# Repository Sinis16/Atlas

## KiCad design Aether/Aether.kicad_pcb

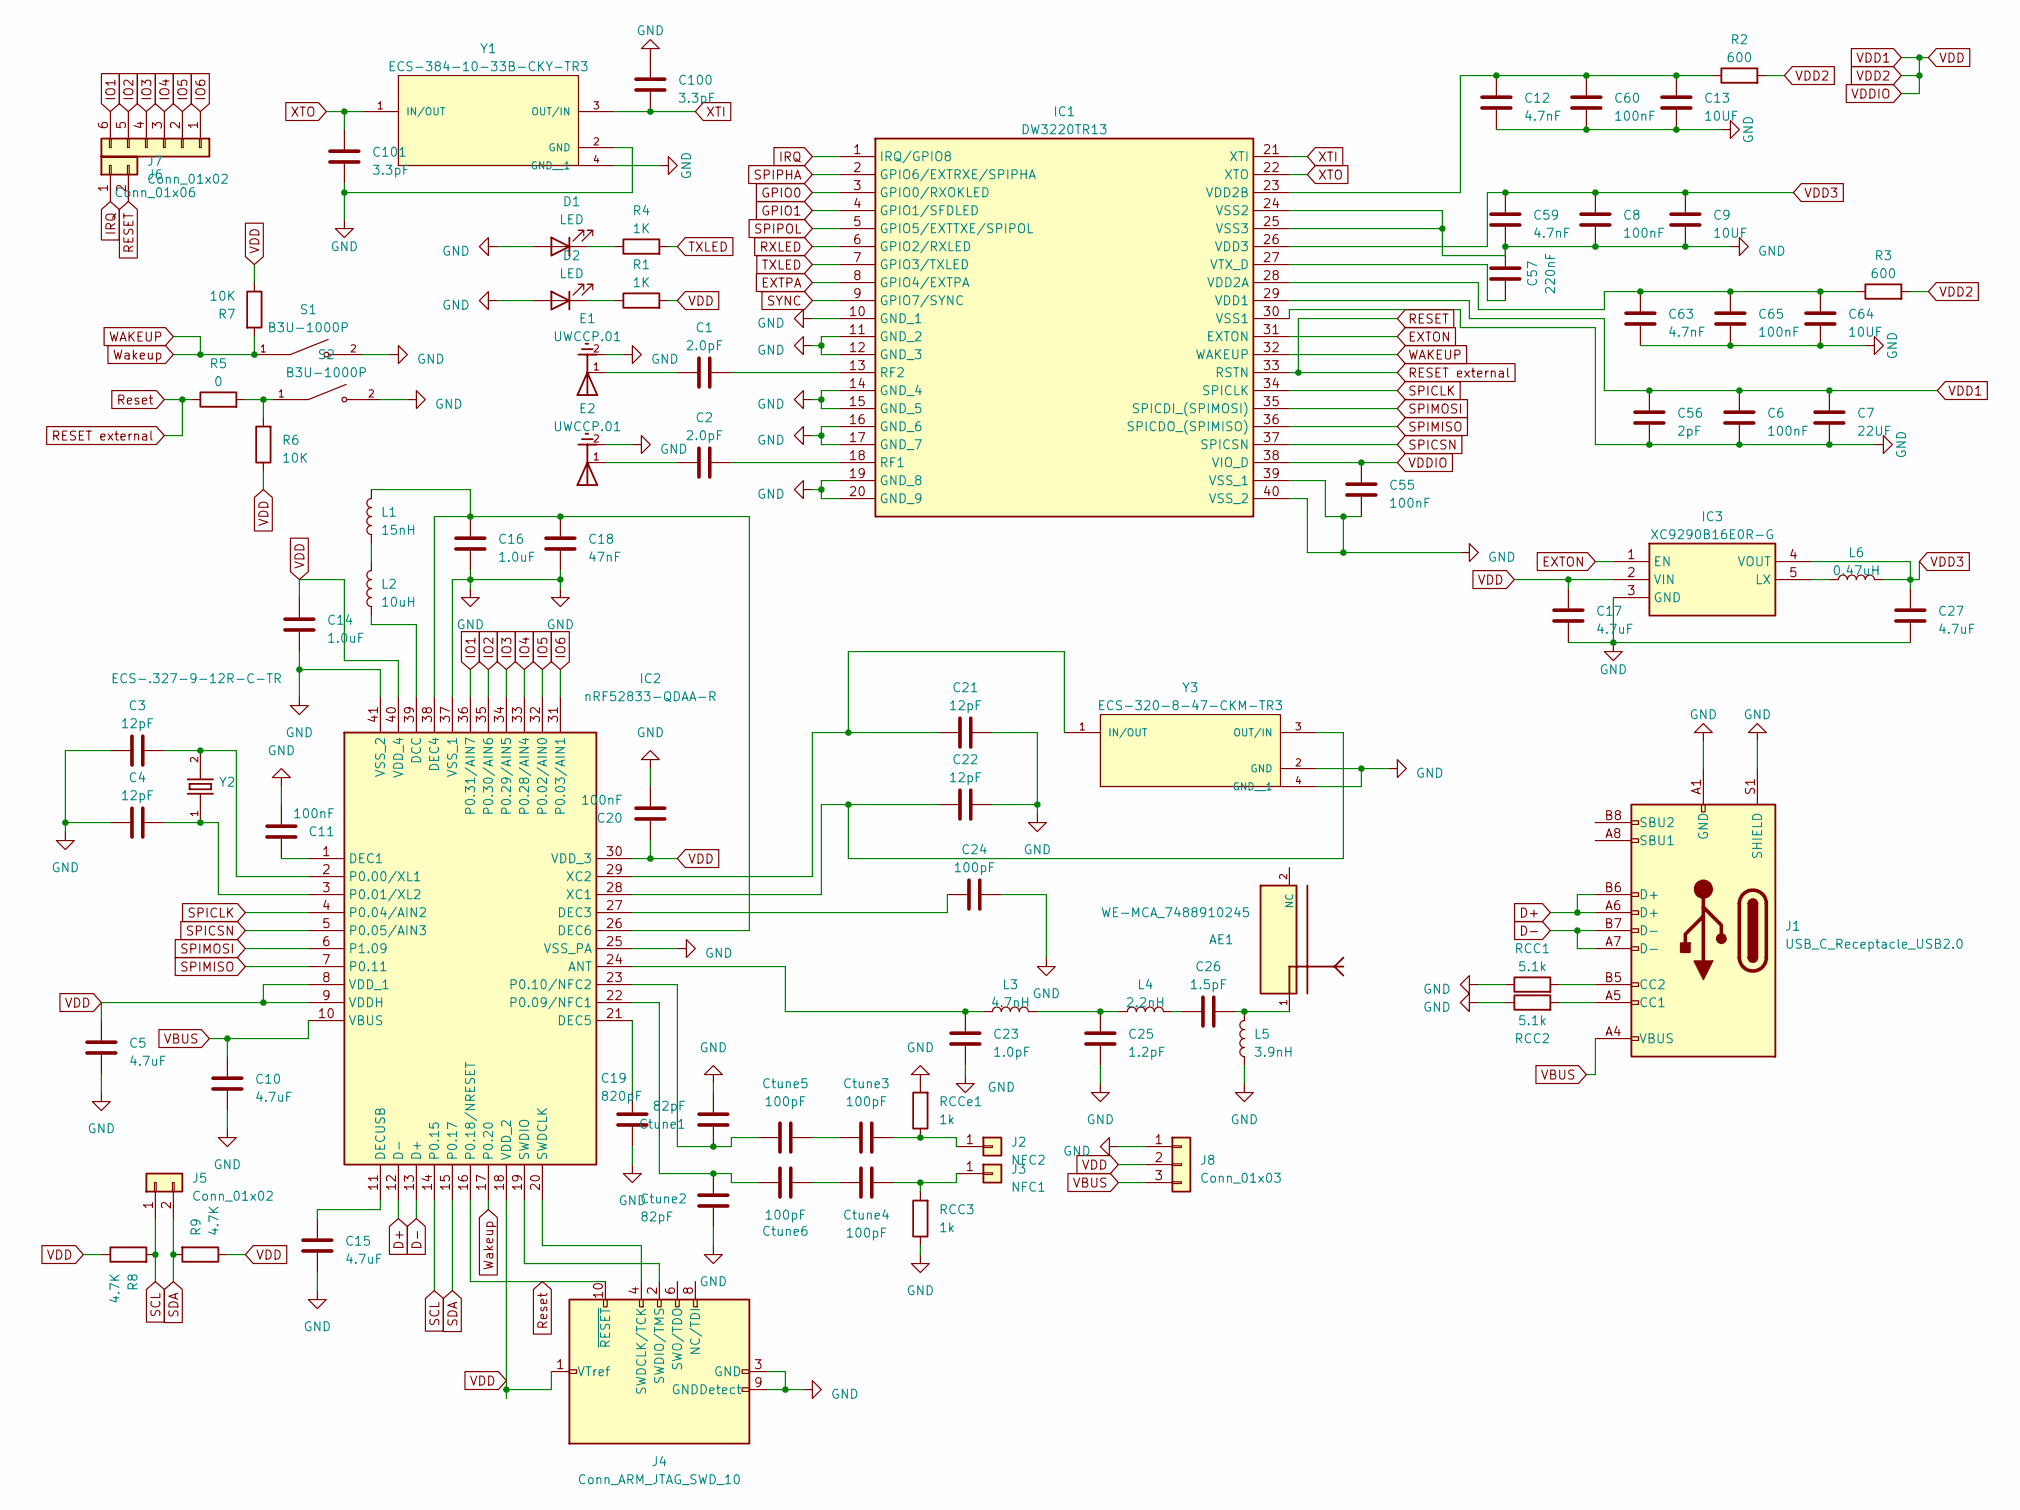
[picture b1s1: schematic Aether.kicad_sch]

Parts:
AE1: WE-MCA_7488910245; PART-NUMBER 7488910245
C1, C2: 2.0pF; C_0201_0603Metric
C3, C4, C21, C22: 12pF; C_0603_1608Metric
C5, C10, C15: 4.7uF; C_0603_1608Metric
C6, C8, C11, C20, C60, C65: 100nF; C_0603_1608Metric
C7: 22UF; C_0603_1608Metric
C9, C13, C64: 10UF; C_0603_1608Metric
C12, C59, C63: 4.7nF; C_0603_1608Metric
C14, C16: 1.0uF; C_0603_1608Metric
C17, C27: 4.7uF; C_0201_0603Metric_Pad0.64x0.40mm_HandSolder
C18: 47nF; C_0603_1608Metric
C19: 820pF; C_0603_1608Metric
C23: 1.0pF; C_0201_0603Metric_Pad0.64x0.40mm_HandSolder
C24: 100pF; C_0603_1608Metric
C25: 1.2pF; C_0201_0603Metric_Pad0.64x0.40mm_HandSolder
C26: 1.5pF; C_0201_0603Metric_Pad0.64x0.40mm_HandSolder
C55: 100nF; C_0402_1005Metric
C56: 2pF; C_0603_1608Metric
C57: 220nF; C_0603_1608Metric
C100, C101: 3.3pF; C_0603_1608Metric
Ctune1, Ctune2: 82pF; C_0603_1608Metric
Ctune3, Ctune4, Ctune5, Ctune6: 100pF; C_0805_2012Metric
D1, D2: LED; LED_0603_1608Metric
E1, E2: UWCCP.01; ANTENNA_UWCCP.01; PARTREV SPE-17-8-057/AZ
IC1: DW3220TR13; DW3220TR13-1; Manufacturer_Part_Number DW3220TR13; Mouser Part Number 772-DW3220TR13
IC2: nRF52833-QDAA-R; QFN40P500X500X90-41N; Manufacturer_Part_Number nRF52833-QDAA-R; Mouser Part Number 949-NRF52833-QDAA-R
IC3: XC9290B16E0R-G; XC9290A07E0RG; Manufacturer_Part_Number XC9290B16E0R-G; Mouser Part Number 865-XC9290B16E0R-G
J1: USB_C_Receptacle_USB2.0; USB_C_Receptacle_Palconn_UTC16-G
J2: NFC2; TestPoint_Pad_3.0x3.0mm
J3: NFC1; TestPoint_Pad_3.0x3.0mm
J4: Conn_ARM_JTAG_SWD_10; PinHeader_2x05_P1.27mm_Vertical
J5, J7: Conn_01x02; PinHeader_1x02_P2.54mm_Vertical
J6: Conn_01x06; PinHeader_1x06_P2.54mm_Vertical
J8: Conn_01x03; PinHeader_1x03_P2.54mm_Vertical
L1: 15nH; L_0603_1608Metric
L2: 10uH; L_0603_1608Metric
L3: 4.7nH; L_0201_0603Metric
L4: 2.2nH; L_0201_0603Metric
L5: 3.9nH; L_0201_0603Metric
L6: 0.47uH; L_01005_0402Metric
R1, R4: 1K; R_0603_1608Metric_Pad0.98x0.95mm_HandSolder
R2, R3: 600; R_0603_1608Metric_Pad0.98x0.95mm_HandSolder
R5: 0; R_0603_1608Metric_Pad0.98x0.95mm_HandSolder
R6, R7: 10K; R_0603_1608Metric_Pad0.98x0.95mm_HandSolder
R8, R9: 4.7K; R_0603_1608Metric_Pad0.98x0.95mm_HandSolder
RCC1, RCC2: 5.1k; R_0603_1608Metric
RCC3: 1k; R_0603_1608Metric
RCCe1: 1k; R_0603_1608Metric
S1, S2: B3U-1000P; SW_B3U-1000P
Y1: ECS-384-10-33B-CKY-TR3; XTAL_ECS-384-10-33B-CKY-TR3; PARTREV 2017
Y2: ECS-.327-9-12R-C-TR; XTAL_ECS-.327-9-12R-C-TR; PARTREV 2017
Y3: ECS-320-8-47-CKM-TR3; XTAL_ECS-320-8-47-CKM-TR3; PARTREV 2017

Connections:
D+: IC2.12 (D-), J1.A6 (D+), J1.B6 (D+)
D-: IC2.13 (D+), J1.A7 (D-), J1.B7 (D-)
EXTON: IC1.31 (EXTON), IC3.1 (EN)
EXTPA: IC1.8 (GPIO4/EXTPA)
GND: C3.2, C4.2, C5.2, C6.1, C7.1, C8.1, C9.1, C10.2, C11.2, C12.1, C13.1, C14.2, C15.2, C16.2, C17.1, C18.2, C19.2, C20.2, C21.2, C22.2, C23.2, C24.2, C25.2, C27.1, C55.1, C56.1, C57.2, C59.1, C60.2, C63.1, C64.1, C65.1, C100.2, C101.1, Ctune1.2, Ctune2.2, D1.2 (A), D2.2 (A), E1.2, E2.2, IC1.10 (GND_1), IC1.11 (GND_2), IC1.12 (GND_3), IC1.14 (GND_4), IC1.15 (GND_5), IC1.16 (GND_6), IC1.17 (GND_7), IC1.19 (GND_8), IC1.20 (GND_9), IC1.24 (VSS2), IC1.25 (VSS3), IC1.30 (VSS1), IC1.39 (VSS_1), IC1.40 (VSS_2), IC2.25 (VSS_PA), IC2.37 (VSS_1), IC2.41 (VSS_2), IC3.3 (GND), J1.A1 (GND), J1.A12 (GND), J1.B1 (GND), J1.B12 (GND), J1.S1 (SHIELD), J4.3 (GND), J4.5 (GND), J4.9 (GNDDetect), J8.1, L5.1, RCC1.1, RCC2.1, RCC3.1, RCCe1.2, S1.2, S2.2, Y1.2 (GND), Y1.4 (GND__1), Y3.2 (GND), Y3.4 (GND__1)
GPIO0: IC1.3 (GPIO0/RXOKLED)
GPIO1: IC1.4 (GPIO1/SFDLED)
IO1: IC2.36 (P0.31/AIN7), J6.6
IO2: IC2.35 (P0.30/AIN6), J6.5
IO3: IC2.34 (P0.29/AIN5), J6.4
IO4: IC2.33 (P0.28/AIN4), J6.3
IO5: IC2.32 (P0.02/AIN0), J6.2
IO6: IC2.31 (P0.03/AIN1), J6.1
IRQ: IC1.1 (IRQ/GPIO8), J7.1
unnamed: AE1.1, C26.1, L5.2
unnamed: C1.2, E1.1
unnamed: C2.2, E2.1
unnamed: C25.1, L3.2, L4.1
unnamed: C26.2, L4.2
unnamed: Ctune3.2, Ctune5.1
unnamed: Ctune4.2, Ctune6.1
unnamed: D1.1 (K), R4.1
unnamed: D2.1 (K), R1.1
unnamed: C2.1, IC1.18 (RF1)
unnamed: C1.1, IC1.13 (RF2)
unnamed: C63.2, C64.2, C65.2, IC1.28 (VDD2A), R3.1
unnamed: C12.2, C13.2, C60.1, IC1.23 (VDD2B), R2.1
unnamed: C57.1, IC1.27 (VTX_D)
unnamed: C23.1, IC2.24 (ANT), L3.1
unnamed: IC2.39 (DCC), L2.1
unnamed: C11.1, IC2.1 (DEC1)
unnamed: C24.1, IC2.27 (DEC3)
unnamed: C16.1, C18.1, IC2.26 (DEC6), IC2.38 (DEC4), L1.2
unnamed: C19.1, IC2.21 (DEC5)
unnamed: C15.1, IC2.11 (DECUSB)
unnamed: C3.1, IC2.2 (P0.00/XL1), Y2.2
unnamed: C4.1, IC2.3 (P0.01/XL2), Y2.1
unnamed: Ctune2.1, Ctune6.2, IC2.22 (P0.09/NFC1)
unnamed: Ctune1.1, Ctune5.2, IC2.23 (P0.10/NFC2)
unnamed: IC2.20 (SWDCLK), J4.4 (SWDCLK/TCK)
unnamed: IC2.19 (SWDIO), J4.2 (SWDIO/TMS)
unnamed: C22.1, IC2.28 (XC1), Y3.3 (OUT/IN)
unnamed: C21.1, IC2.29 (XC2), Y3.1 (IN/OUT)
unnamed: IC3.5 (LX), L6.1
unnamed: J1.A5 (CC1), RCC2.2
unnamed: J1.B5 (CC2), RCC1.2
unnamed: Ctune3.1, J2.1, RCCe1.1
unnamed: Ctune4.1, J3.1, RCC3.2
unnamed: L1.1, L2.2
unnamed: R5.2, R6.2, S2.1
RESET: IC1.33 (RSTN), IC2.16 (P0.18/NRESET), J4.10 (~RESET), J7.2, R5.1
RXLED: IC1.6 (GPIO2/RXLED)
SCL: IC2.14 (P0.15), J5.1, R8.2
SDA: IC2.15 (P0.17), J5.2, R9.2
SPICLK: IC1.34 (SPICLK), IC2.4 (P0.04/AIN2)
SPICSN: IC1.37 (SPICSN), IC2.5 (P0.05/AIN3)
SPIMISO: IC1.36 (SPICDO_(SPIMISO)), IC2.7 (P0.11)
SPIMOSI: IC1.35 (SPICDI_(SPIMOSI)), IC2.6 (P1.09)
SPIPHA: IC1.2 (GPIO6/EXTRXE/SPIPHA)
SPIPOL: IC1.5 (GPIO5/EXTTXE/SPIPOL)
SYNC: IC1.9 (GPIO7/SYNC)
TXLED: IC1.7 (GPIO3/TXLED), R4.2
VBUS: C10.1, IC2.10 (VBUS), J1.A4 (VBUS), J1.A9 (VBUS), J1.B4 (VBUS), J1.B9 (VBUS), J8.3
VDD: C5.1, C6.2, C7.2, C14.1, C17.2, C20.1, C55.2, C56.2, IC1.29 (VDD1), IC1.38 (VIO_D), IC2.8 (VDD_1), IC2.9 (VDDH), IC2.18 (VDD_2), IC2.30 (VDD_3), IC2.40 (VDD_4), IC3.2 (VIN), J4.1 (VTref), J8.2, R1.2, R2.2, R3.2, R6.1, R7.1, R8.1, R9.1
VDD3: C8.2, C9.2, C27.2, C59.2, IC1.26 (VDD3), IC3.4 (VOUT), L6.2
WAKEUP: IC1.32 (WAKEUP), IC2.17 (P0.20), R7.2, S1.1
XTI: C100.1, IC1.21 (XTI), Y1.3 (OUT/IN)
XTO: C101.2, IC1.22 (XTO), Y1.1 (IN/OUT)

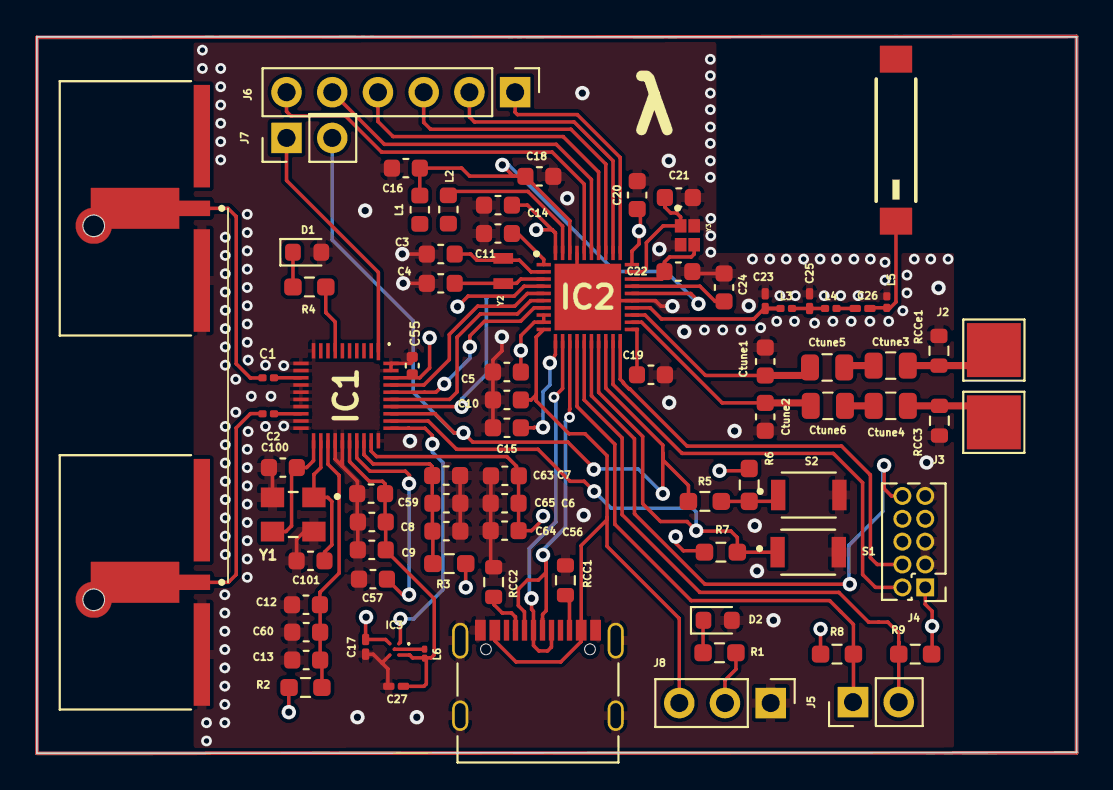
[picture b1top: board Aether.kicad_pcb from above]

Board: 4 copper layers, 57.8 x 39.8 mm, 83 parts (0 on the bottom side), 61 nets.

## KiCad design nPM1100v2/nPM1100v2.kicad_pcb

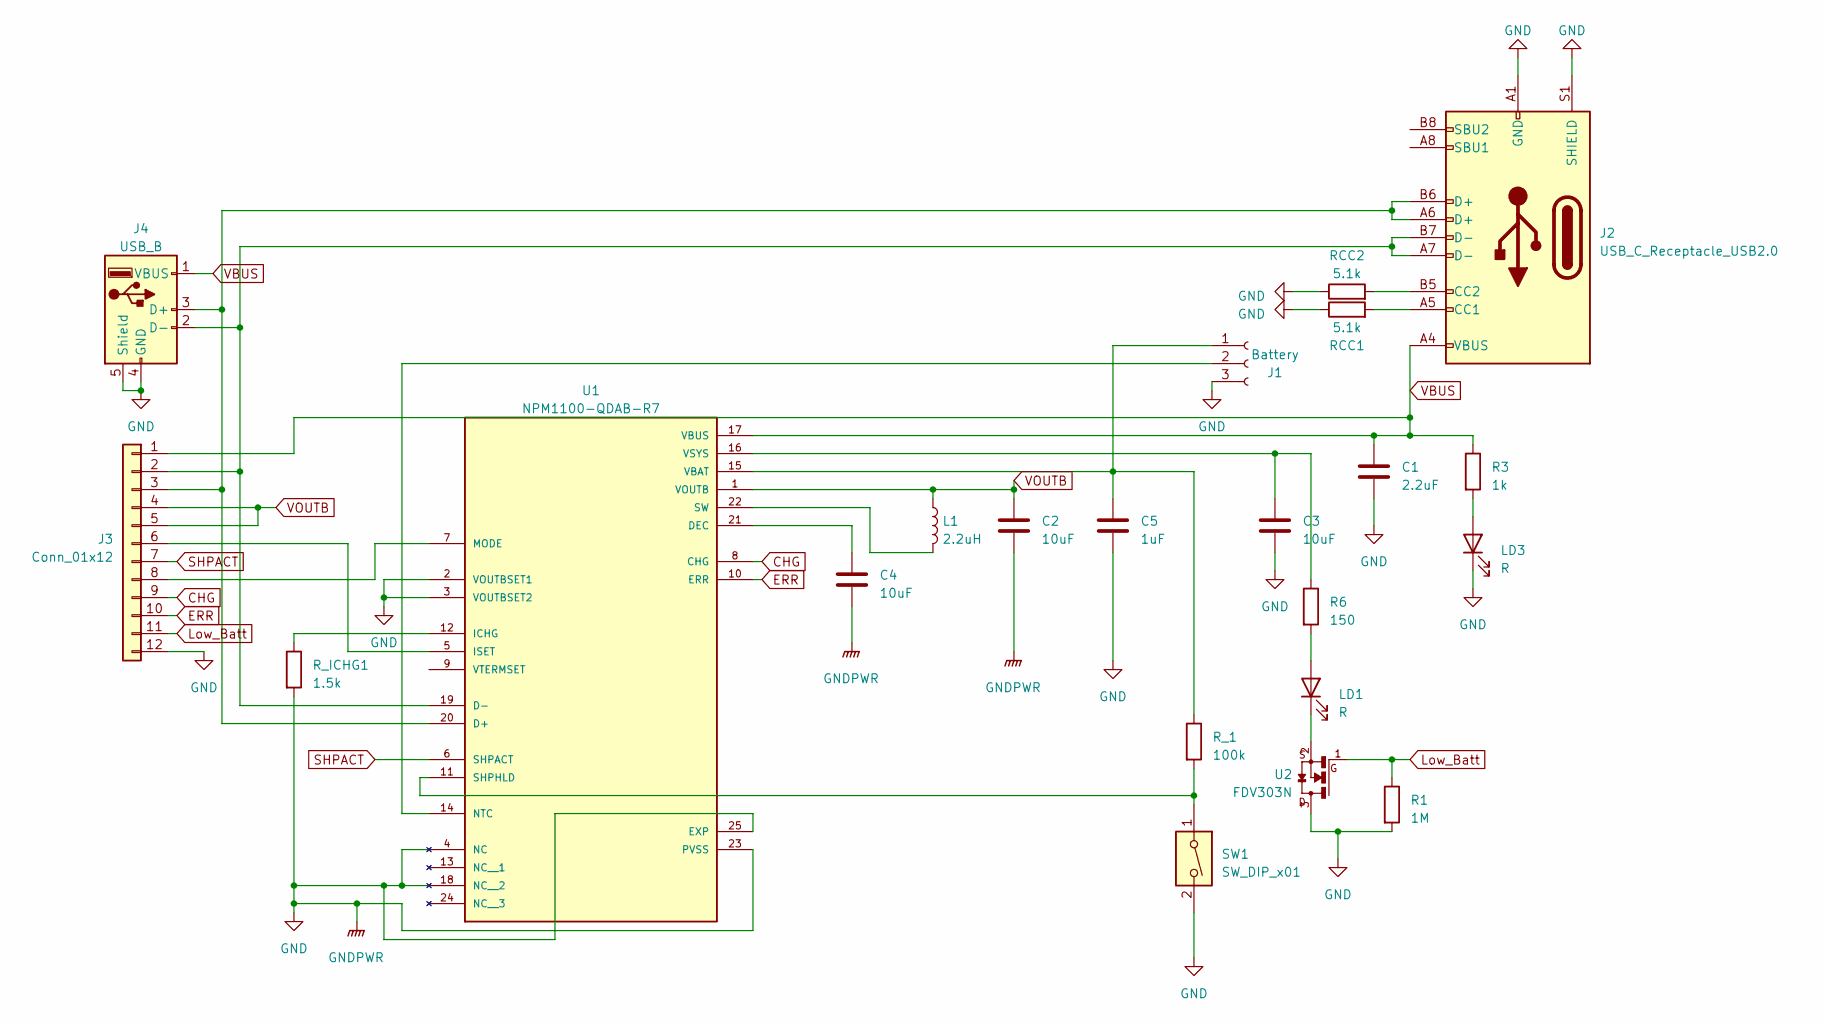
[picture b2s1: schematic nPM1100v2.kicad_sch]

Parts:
C1: 2.2uF; C_0603_1608Metric
C2, C3, C4: 10uF; C_0603_1608Metric
C5: 1uF; C_0603_1608Metric
J1: Battery; JST_XH_B3B-XH-A_1x03_P2.50mm_Vertical
J2: USB_C_Receptacle_USB2.0; USB_C_Receptacle_Palconn_UTC16-G
J3: Conn_01x12; PinHeader_1x12_P2.54mm_Vertical
J4: USB_B; USB_A_TE_292303-7_Horizontal
L1: 2.2uH; L_0805_2012Metric
LD1, LD3: R; LED_0201_0603Metric
R1: 1M; R_0201_0603Metric
R3: 1k; R_0201_0603Metric
R6: 150; R_0201_0603Metric
RCC1, RCC2: 5.1k; R_0201_0603Metric
R_1: 100k; R_0201_0603Metric
R_ICHG1: 1.5k; R_0201_0603Metric
SW1: SW_DIP_x01; SW_B3U-1000P
U1: NPM1100-QDAB-R7; QFN50P400X400X90-25N; PARTREV 1.3
U2: FDV303N; SOT23

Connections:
CHG: J3.9, U1.8 (CHG)
ERR: J3.10, U1.10 (ERR)
GND: C1.2, C2.2, C3.2, C4.2, C5.2, J1.3, J2.A1 (GND), J2.A12 (GND), J2.B1 (GND), J2.B12 (GND), J2.S1 (SHIELD), J3.12, J4.4 (GND), J4.5 (Shield), LD3.1 (K), R1.2, RCC1.1, RCC2.1, R_ICHG1.2, SW1.2, U1.2 (VOUTBSET1), U1.3 (VOUTBSET2), U1.4 (NC), U1.18 (NC__2), U1.23 (PVSS), U1.25 (EXP), U2.3
Low_Batt: J3.11, R1.1, U2.1
unnamed: C5.1, J1.1, R_1.1, U1.15 (VBAT)
unnamed: J1.2, U1.14 (NTC)
unnamed: J2.A5 (CC1), RCC1.2
unnamed: J2.B5 (CC2), RCC2.2
unnamed: J2.A7 (D-), J2.B7 (D-), J3.2, J4.2 (D-), U1.19 (D-)
unnamed: J2.A6 (D+), J2.B6 (D+), J3.3, J4.3 (D+), U1.20 (D+)
unnamed: J3.6, U1.5 (ISET)
unnamed: J3.8, U1.7 (MODE)
unnamed: LD1.2 (A), R6.2
unnamed: LD1.1 (K), U2.2
unnamed: LD3.2 (A), R3.2
unnamed: C4.1, U1.21 (DEC)
unnamed: R_ICHG1.1, U1.12 (ICHG)
unnamed: R_1.2, SW1.1, U1.11 (SHPHLD)
unnamed: L1.2, U1.22 (SW)
unnamed: C3.1, R6.1, U1.16 (VSYS)
SHPACT: J3.7, U1.6 (SHPACT)
VBUS: C1.1, J2.A4 (VBUS), J2.A9 (VBUS), J2.B4 (VBUS), J2.B9 (VBUS), J3.1, J4.1 (VBUS), R3.1, U1.17 (VBUS)
VOUTB: C2.1, J3.4, J3.5, L1.1, U1.1 (VOUTB)

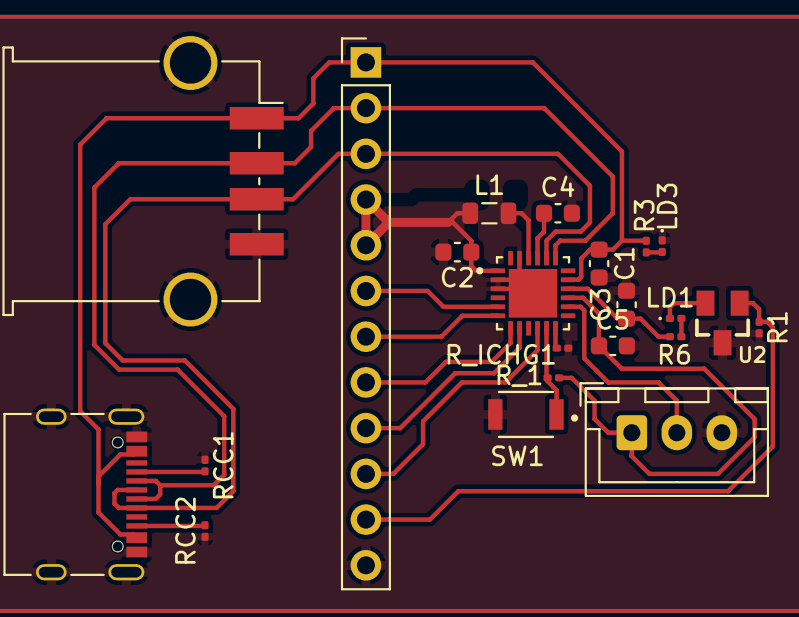
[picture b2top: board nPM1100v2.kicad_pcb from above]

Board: 2 copper layers, 22 parts (0 on the bottom side), 23 nets.

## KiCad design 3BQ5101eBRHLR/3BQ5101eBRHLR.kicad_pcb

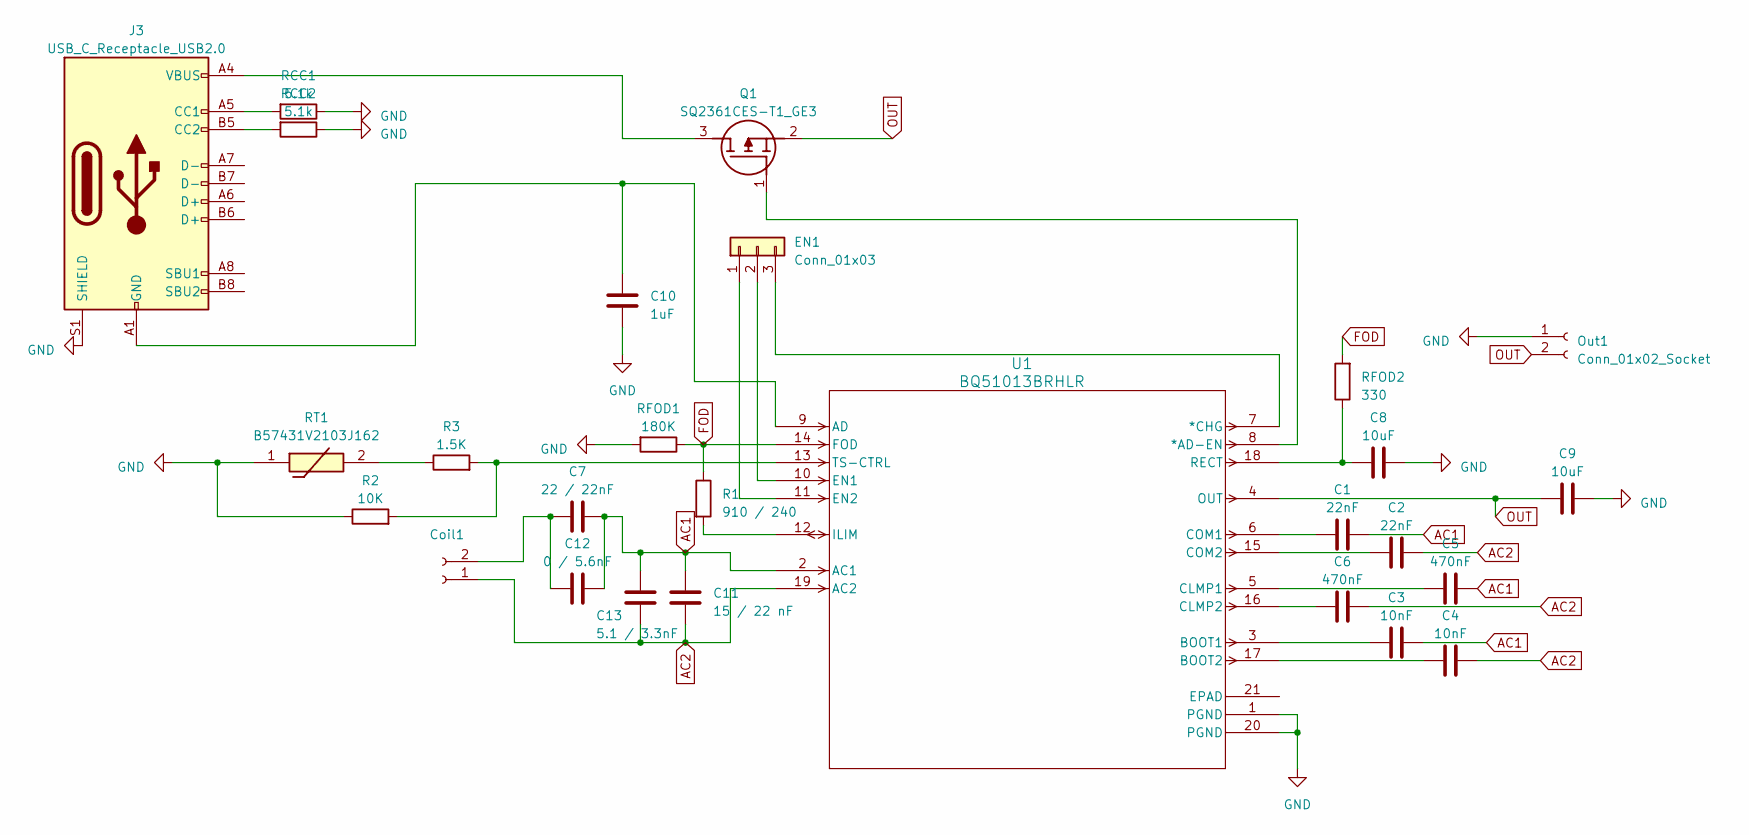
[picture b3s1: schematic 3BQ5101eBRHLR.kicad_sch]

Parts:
C1, C2: 22nF; C_0603_1608Metric
C3, C4: 10nF; C_0603_1608Metric
C5, C6: 470nF; C_0603_1608Metric
C7: 22 / 22nF; C_0603_1608Metric
C8, C9: 10uF; C_0603_1608Metric
C10: 1uF; C_0603_1608Metric
C11: 15 / 22 nF; C_0603_1608Metric
C12: 0 / 5.6nF; C_0603_1608Metric
C13: 5.1 / 3.3nF; C_0603_1608Metric
Coil1: TerminalBlock_bornier-2_P5.08mm
EN1: Conn_01x03; PinSocket_1x03_P2.54mm_Vertical
J3: USB_C_Receptacle_USB2.0; USB_C_Receptacle_Palconn_UTC16-G
Out1: Conn_01x02_Socket; PinSocket_1x02_P2.54mm_Vertical
Q1: SQ2361CES-T1_GE3; SOT95P237X112-3N; Mouser Part Number 78-SQ2361CES-T1_GE3
R1: 910 / 240; R_0603_1608Metric
R2: 10K; R_0603_1608Metric
R3: 1.5K; R_0603_1608Metric
RCC1, RCC2: 5.1k; R_0603_1608Metric
RFOD1: 180K; R_0603_1608Metric
RFOD2: 330; R_0603_1608Metric
RT1: B57431V2103J162; THRMC2012X50N; Manufacturer_Part_Number NTC0805J2K0; Mouser Part Number 279-NTC0805J2K0
U1: BQ51013BRHLR; BQ5101eBRHLR

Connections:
AC1: C1.2, C3.2, C5.2, C7.2, C11.2, C12.2, C13.2, U1.2 (AC1)
AC2: C2.2, C4.2, C6.2, C11.1, C13.1, Coil1.1, U1.19 (AC2)
FOD: R1.1, RFOD1.1, RFOD2.2, U1.14 (FOD)
GND: C8.2, C9.2, C10.1, J3.S1 (SHIELD), Out1.1, R2.1, RCC1.1, RCC2.1, RFOD1.2, RT1.1, U1.1 (PGND), U1.20 (PGND)
unnamed: C7.1, C12.1, Coil1.2
unnamed: EN1.1, U1.11 (EN2)
unnamed: EN1.2, U1.10 (EN1)
unnamed: EN1.3, U1.7 (*CHG)
unnamed: J3.A5 (CC1), RCC1.2
unnamed: J3.B5 (CC2), RCC2.2
unnamed: J3.A4 (VBUS), J3.A9 (VBUS), J3.B4 (VBUS), J3.B9 (VBUS), Q1.3 (D)
unnamed: Q1.1 (G), U1.8 (*AD-EN)
unnamed: R3.1, RT1.2
unnamed: C10.2, J3.A1 (GND), J3.A12 (GND), J3.B1 (GND), J3.B12 (GND), U1.9 (AD)
unnamed: C3.1, U1.3 (BOOT1)
unnamed: C4.1, U1.17 (BOOT2)
unnamed: C5.1, U1.5 (CLMP1)
unnamed: C6.1, U1.16 (CLMP2)
unnamed: C1.1, U1.6 (COM1)
unnamed: C2.1, U1.15 (COM2)
unnamed: R1.2, U1.12 (ILIM)
unnamed: C8.1, RFOD2.1, U1.18 (RECT)
unnamed: R2.2, R3.2, U1.13 (TS-CTRL)
OUT: C9.1, Out1.2, Q1.2 (S), U1.4 (OUT)

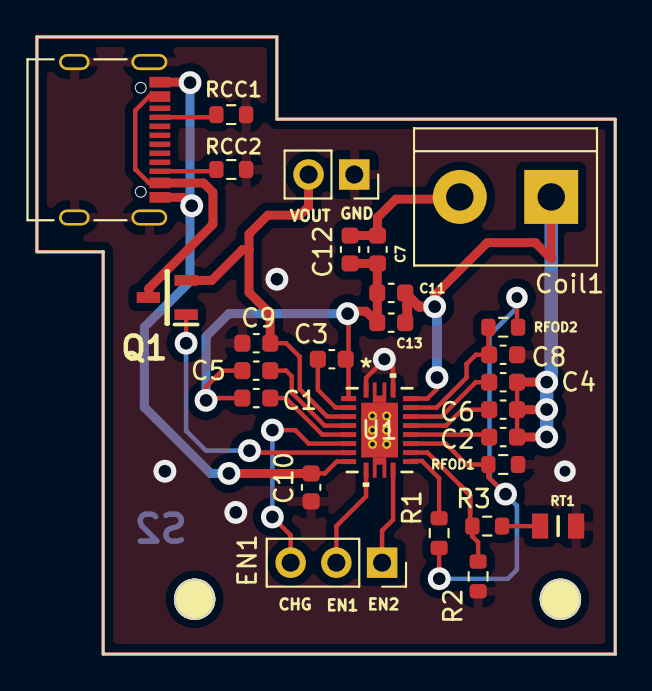
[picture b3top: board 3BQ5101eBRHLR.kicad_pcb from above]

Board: 2 copper layers, 32.1 x 34.3 mm, 27 parts (0 on the bottom side), 24 nets.

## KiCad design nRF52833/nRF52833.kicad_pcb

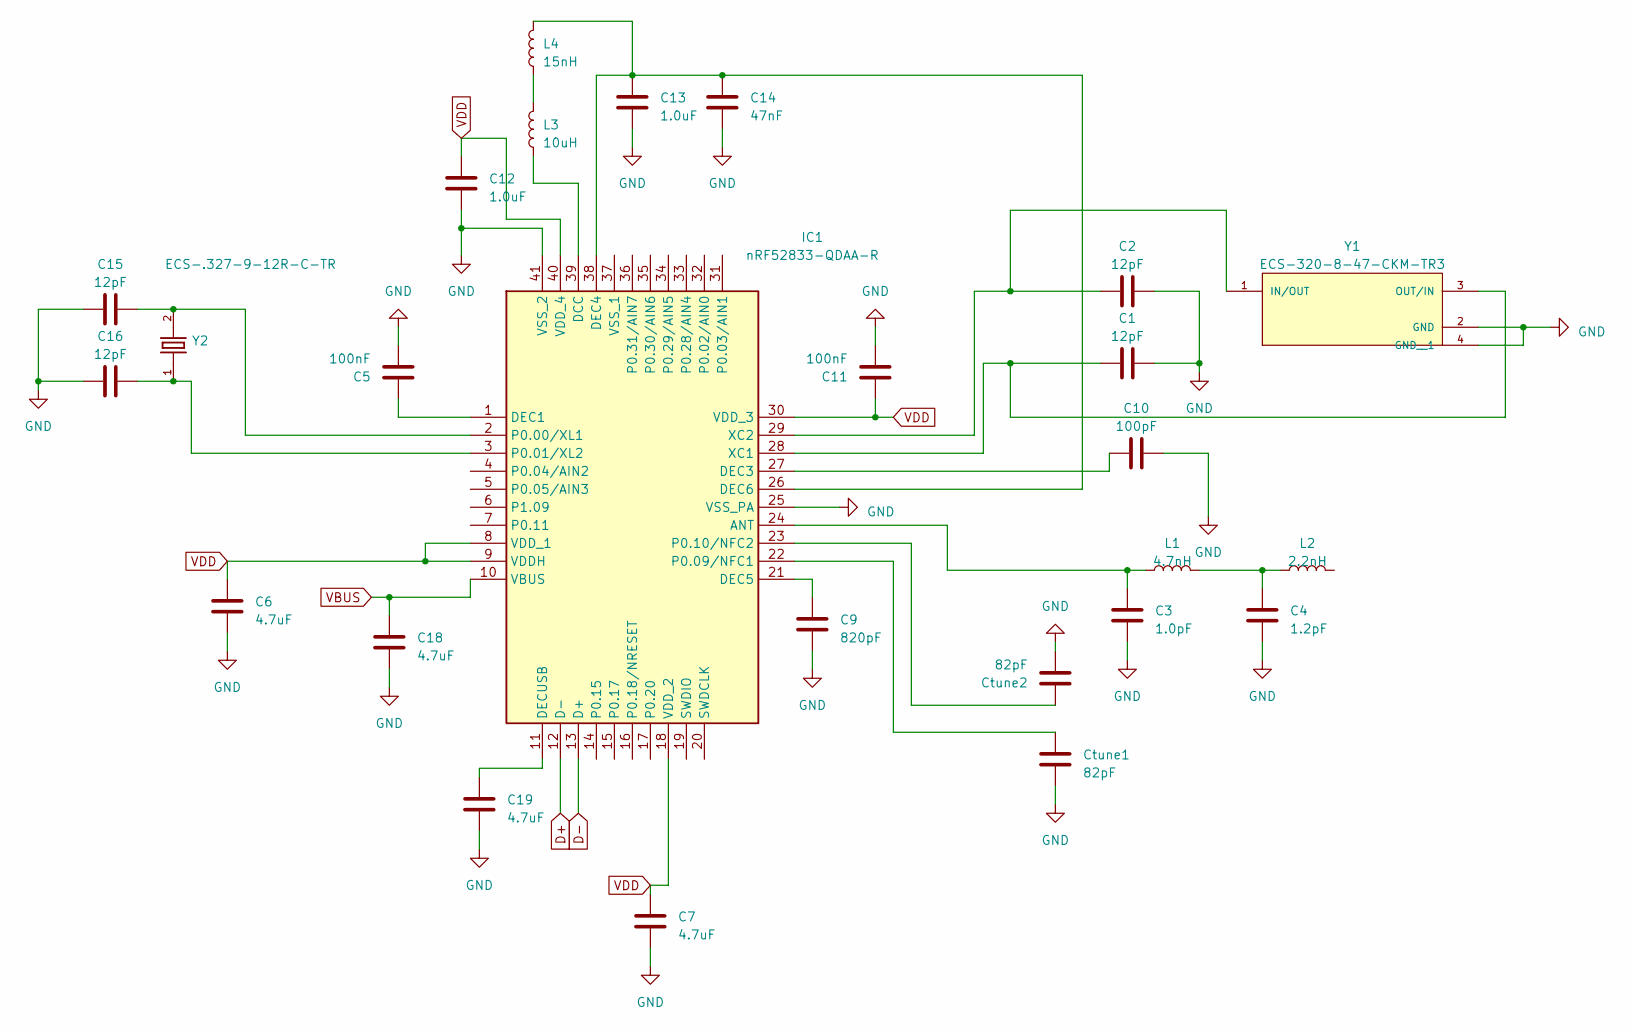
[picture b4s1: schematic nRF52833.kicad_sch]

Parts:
C1, C2, C15, C16: 12pF; C_0603_1608Metric
C3: 1.0pF; C_0603_1608Metric
C4: 1.2pF; C_0603_1608Metric
C5, C11: 100nF; C_0603_1608Metric
C6, C7, C18, C19: 4.7uF; C_0603_1608Metric
C9: 820pF; C_0603_1608Metric
C10: 100pF; C_0603_1608Metric
C12, C13: 1.0uF; C_0603_1608Metric
C14: 47nF; C_0603_1608Metric
Ctune1, Ctune2: 82pF; C_0603_1608Metric
IC1: nRF52833-QDAA-R; QFN40P500X500X90-41N; Manufacturer_Part_Number nRF52833-QDAA-R; Mouser Part Number 949-NRF52833-QDAA-R
L1: 4.7nH; L_0603_1608Metric
L2: 2.2nH; L_0603_1608Metric
L3: 10uH; L_0603_1608Metric
L4: 15nH; L_0603_1608Metric
Y1: ECS-320-8-47-CKM-TR3; XTAL_ECS-320-8-47-CKM-TR3; PARTREV 2017
Y2: ECS-.327-9-12R-C-TR; XTAL_ECS-.327-9-12R-C-TR; PARTREV 2017

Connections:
D+: IC1.12 (D-)
D-: IC1.13 (D+)
GND: C1.2, C2.2, C3.2, C4.2, C5.2, C6.2, C7.2, C9.2, C10.2, C11.2, C12.2, C13.2, C14.2, C15.2, C16.2, C18.2, C19.2, Ctune1.2, Ctune2.2, IC1.25 (VSS_PA), IC1.41 (VSS_2), Y1.2 (GND), Y1.4 (GND__1)
unnamed: C4.1, L1.2, L2.1
unnamed: C3.1, IC1.24 (ANT), L1.1
unnamed: IC1.39 (DCC), L3.1
unnamed: C5.1, IC1.1 (DEC1)
unnamed: C10.1, IC1.27 (DEC3)
unnamed: C13.1, C14.1, IC1.26 (DEC6), IC1.38 (DEC4), L4.2
unnamed: C9.1, IC1.21 (DEC5)
unnamed: C19.1, IC1.11 (DECUSB)
unnamed: C15.1, IC1.2 (P0.00/XL1), Y2.2
unnamed: C16.1, IC1.3 (P0.01/XL2), Y2.1
unnamed: Ctune1.1, IC1.22 (P0.09/NFC1)
unnamed: Ctune2.1, IC1.23 (P0.10/NFC2)
unnamed: C1.1, IC1.28 (XC1), Y1.3 (OUT/IN)
unnamed: C2.1, IC1.29 (XC2), Y1.1 (IN/OUT)
unnamed: L3.2, L4.1
VBUS: C18.1, IC1.10 (VBUS)
VDD: C6.1, C7.1, C11.1, C12.1, IC1.8 (VDD_1), IC1.9 (VDDH), IC1.18 (VDD_2), IC1.30 (VDD_3), IC1.40 (VDD_4)

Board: 2 copper layers, 26 parts (0 on the bottom side), 18 nets, no tracks yet.

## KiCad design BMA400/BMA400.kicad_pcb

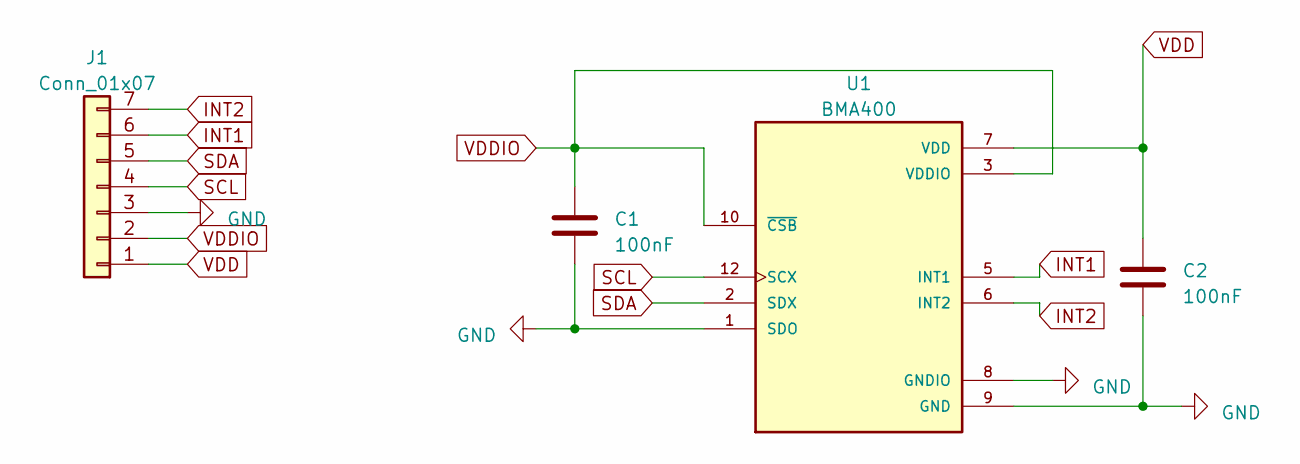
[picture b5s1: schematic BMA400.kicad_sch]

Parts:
C1, C2: 100nF; C_0603_1608Metric
J1: Conn_01x07; PinSocket_1x07_P2.54mm_Vertical
U1: BMA400; XDCR_BMA400

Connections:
GND: C1.2, C2.2, J1.3, U1.1 (SDO), U1.8 (GNDIO), U1.9 (GND)
INT1: J1.6, U1.5 (INT1)
INT2: J1.7, U1.6 (INT2)
SCL: J1.4, U1.12 (SCX)
SDA: J1.5, U1.2 (SDX)
VDD: C2.1, J1.1, U1.7 (VDD)
VDDIO: C1.1, J1.2, U1.3 (VDDIO), U1.10 (~CSB)

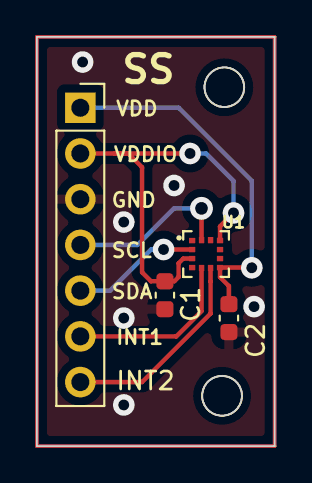
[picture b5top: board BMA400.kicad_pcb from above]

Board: 2 copper layers, 13.2 x 22.7 mm, 4 parts (0 on the bottom side), 7 nets.

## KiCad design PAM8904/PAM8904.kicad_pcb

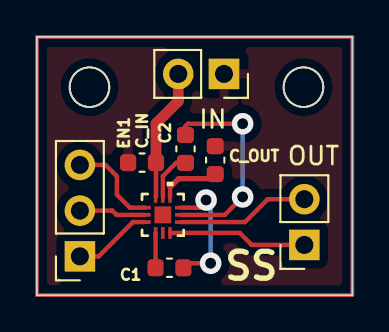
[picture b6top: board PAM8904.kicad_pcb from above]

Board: 2 copper layers, 17.5 x 14.4 mm, 8 parts (0 on the bottom side), 12 nets.

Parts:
C1, C2: 1uF; C_0603_1608Metric
C_IN: 2.2uF; C_0603_1608Metric
C_OUT: 2.2uF; C_0603_1608Metric
EN1: Conn_01x02_Socket; PinSocket_1x03_P2.54mm_Vertical
IN: Conn_01x03_Socket; PinSocket_1x02_P2.54mm_Vertical
OUT: Conn_01x02_Socket; PinSocket_1x02_P2.54mm_Vertical
PAM8904EGPR1: QFN-12_PAM8904EGPR_DIO

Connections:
GND: C_IN.2, C_OUT.2, IN.1, PAM8904EGPR1.5 (GND)
unnamed: EN1.1, PAM8904EGPR1.3 (DIN)
unnamed: EN1.2, PAM8904EGPR1.2 (EN2)
unnamed: EN1.3, PAM8904EGPR1.1 (EN1)
unnamed: C_IN.1, IN.2, PAM8904EGPR1.12 (VIN)
unnamed: OUT.1, PAM8904EGPR1.6 (VO2)
unnamed: OUT.2, PAM8904EGPR1.7 (VO1)
unnamed: C1.1, PAM8904EGPR1.4 (CN1)
unnamed: C2.1, PAM8904EGPR1.8 (CN2)
unnamed: C1.2, PAM8904EGPR1.9 (CP1)
unnamed: C2.2, PAM8904EGPR1.11 (CP2)
unnamed: C_OUT.1, PAM8904EGPR1.10 (VOUT)

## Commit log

2025-03-27 Addfiles
2025-03-31 Nuevo Aether
